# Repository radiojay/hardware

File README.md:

RadioJay Hardware Design
========================

This repo has various hardware designs for RadioJay wildlife tracking tags.
The first few were called "Mostag" for "Motus Open Source TAG" and then later rebranded to RadioJay.
The tags are listed here more or less in reverse chronological order.

For write-ups about these tags see the [RadioJay](https://radiojay.org) web site.

### RadioJay G1 - LoRaWAN+GPS tag

This is a collection of test & dev boards using a bit more space and with connectors to
attach probes and to swap between solar panels and GPS modules.

- [RadioJayG1-ublox](./RadioJayG1-ublox/) has a U-Blox Mia-M10Q GPS and an stm32wle5
  microcontroller with integrated LoRa radio.
- [RadioJayG1-lr1110](./RadioJayG1-lr1110/) has an LR1110 radio with snapshot GPS and with LoRa
  support and uses an stm32u083 microcontroller.
- [RadioJayG1-aem](./RadioJayG1-aem/) is a solar + battery module using an e-Peas AEM10330 energy
  harvesting chip with integrated buck converter; it can be used with a PowerFilm or an IXOLAR
  solar cell and with a LiPO or an LTO battery.
- [RadioJayG1-lr1110](./RadioJayG1-lr1110/) is a solar/battery module using an IXOLAR solar cell
  with an MPP volatge of 4.4V allowing direct charge without boost converter; it has a low Iq
  buck converter to output 1.8V

### RadioJay A2 / MostagV2

First real tag using FlexPCB with a target weight of 1g all-in (incl. loop harness).
Uses uC, Nichicon battery, PowerFilm solar, bq25504, and accelerometer
as well as altimeter (barometer)

#### RadioJay A2a / MostagV2a

Same board with layout changes to satisfy OSH Park's design rules.

### PgmAdapterV2

Adapter board for programming RadioJay A2MostagV2 using a simple USB-serial adapter chip.
Has connectors to attach various types of programming/debug probes.
Most likely not what "normal users" will use, but useful for development.

### RadioJay A1 / MostagV1

Initial proof of concept board, not for strapping to any animal, has uC,
Seiko battery, PowerFilm solar cell, bq25504, and accelerometer, plus linx antenna.

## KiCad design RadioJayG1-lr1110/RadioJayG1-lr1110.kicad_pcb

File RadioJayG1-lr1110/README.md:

RadioJay G1 - LR1110
====================

Test & dev board for a Semtech LR1110, providing GPS snapshot functionality as well as LoRa radio.
A STM32U083 is used as microcontroller for its low power features, familiarity with its peripherals,
and its 256KB flash, which can be used to store GPS data.

The main purpose of the board is to prototype all the pieces and be able to measure power consumption.

Open questions that came up while designing the board:
- Is it possible to get away without 900Mhz RF switch, as one can with the stm32wle?
  The stm32wle datasheet has a footnote in the "sub-Ghz radio characteristics" stating
  "When not in RX operation mode up to 22 dBm is accepted [on RFI_P/RFI_N]". Neither the
  sx1262 nor the lr1110 datasheet have this note so it's not clear whether this is a feature added
  by ST when integrating the sx1262 or whether it's something Semtech doesn't feel the need to specify.
- Can the GPS LNA power be supplied by the LR1110, eliminating one awkward to route signal. The
  datasheet doesn't specify max source current but it does spec minimum V-high voltage @2.5mA,
  which is the typ consumption of the LNA (max is 3.5mA).
- What are the power consumption implications of having only one 32.768kHz xtal and routing the
  clock from the stm32u083 to the LR1110?
- Would rotating the stm32u883 improve the routing?
- What are the minimum RF test points needed in the "final" tag?

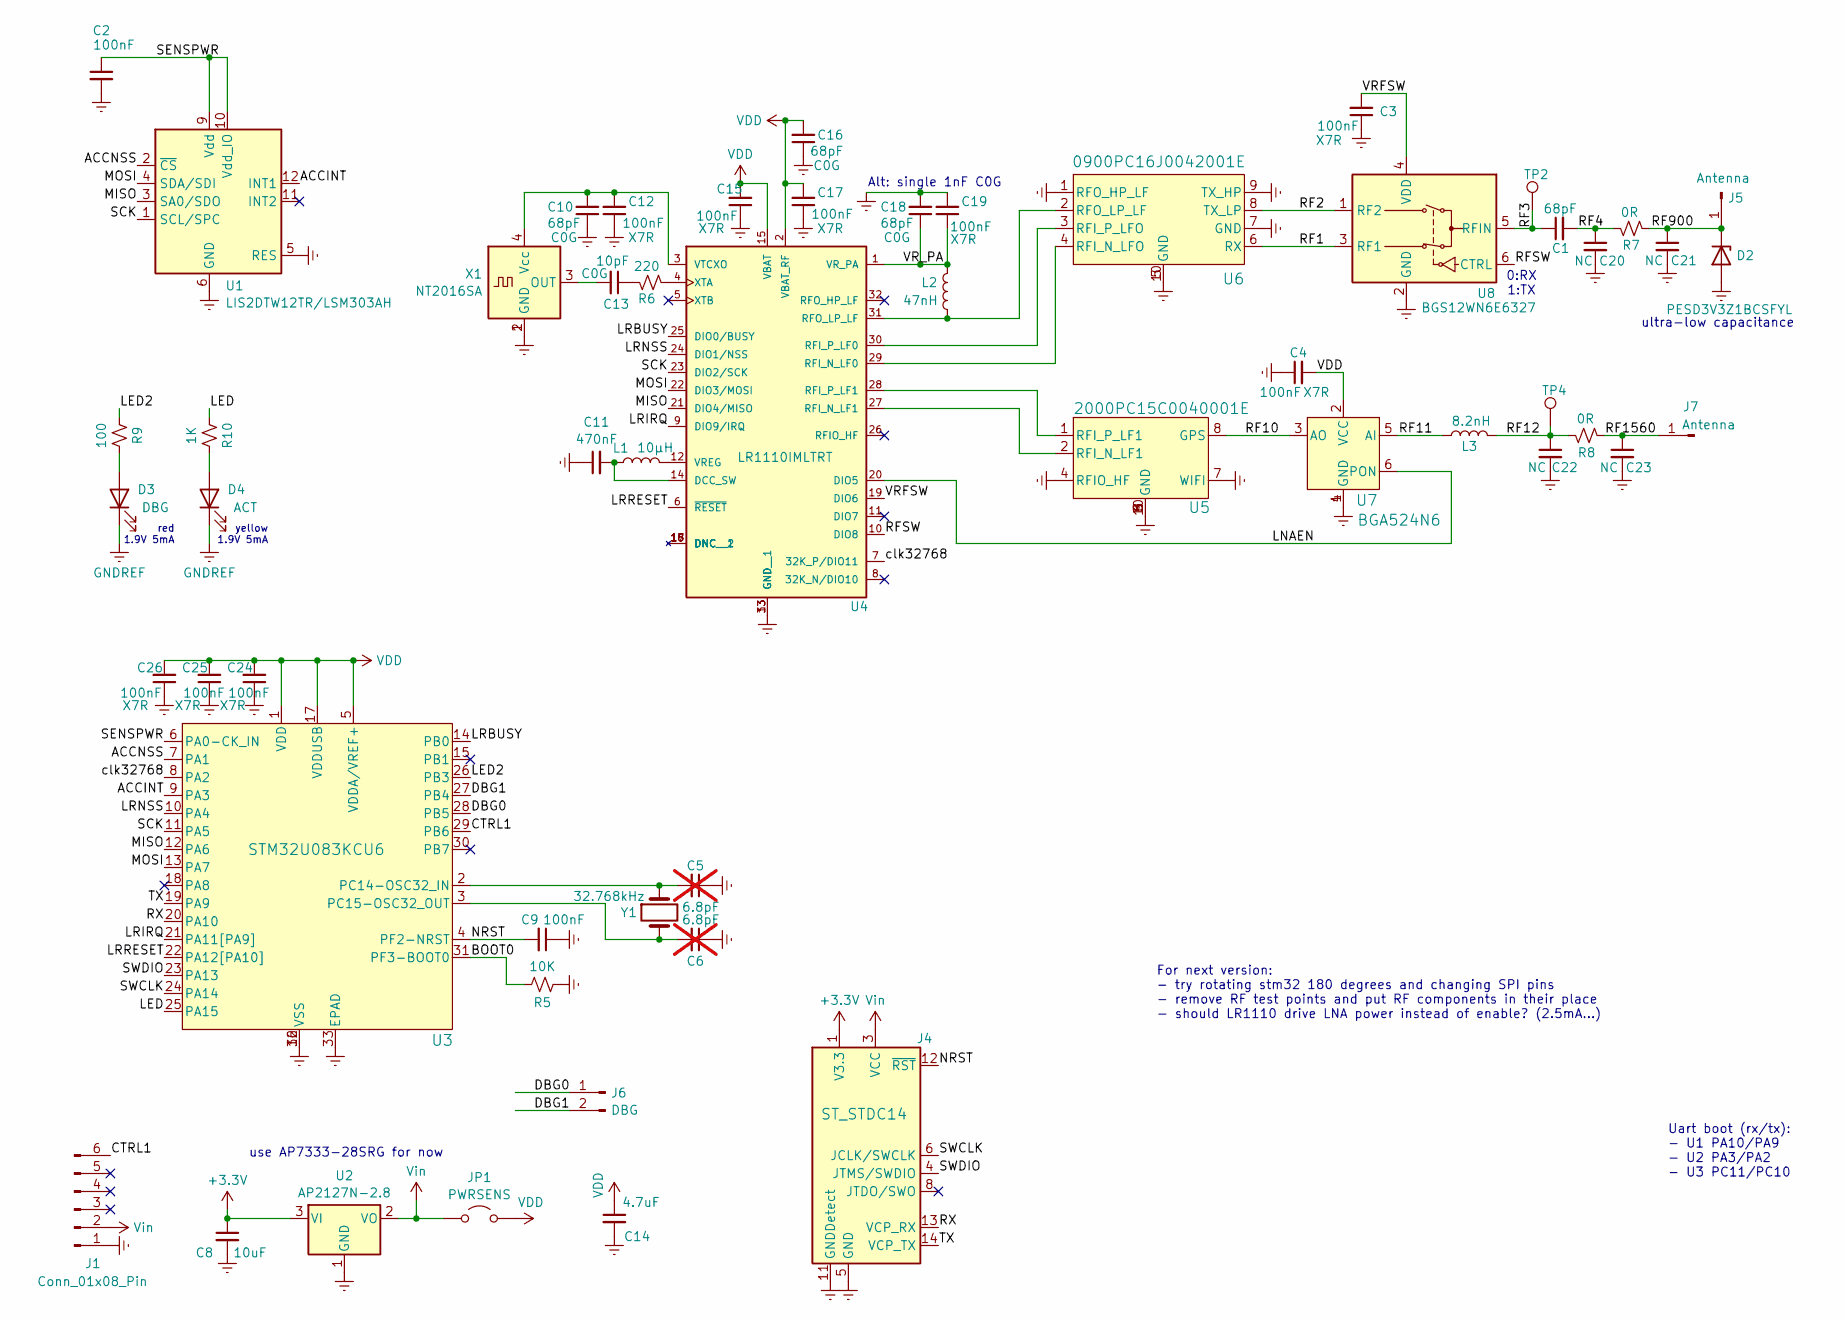
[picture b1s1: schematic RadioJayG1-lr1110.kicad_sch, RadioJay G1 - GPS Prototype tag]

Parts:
C1, C10, C16, C18: 68pF; C_0402_1005Metric
C2, C3, C4, C9, C12, C15, C17, C19, C24, C25, C26: 100nF; C_0402_1005Metric
C5, C6: 6.8pF; C_0402_1005Metric; not fitted
C8: 10uF; C_0603_1608Metric
C11: 470nF; C_0402_1005Metric
C13: 10pF; C_0402_1005Metric
C14: 4.7uF; C_0402_1005Metric
C20, C21, C22, C23: NC; C_0402_1005Metric
D2: PESD3V3Z1BCSFYL; Nexperia_DSN0603-2_0.6x0.3mm_P0.4mm
D3: DBG; LED_0402_1005Metric
D4: ACT; LED_0402_1005Metric
J1: Conn_01x08_Pin; PinHeader_1x06_P2.54mm_Vertical
J4: ST_STDC14; PinHeader_2x07_P1.27mm_Vertical
J5, J7: Antenna; ANT_PAD_2sided_3x2mm
J6: DBG; PinHeader_1x02_P2.54mm_Vertical
JP1: PWRSENS; PinHeader_1x02_P2.54mm_Vertical
L1: 10µH; L_0603_1608Metric; Part MLZ1608N100LT
L2: 47nH; L_0402_1005Metric; Part LQW15AN56NG00
L3: 8.2nH; L_0402_1005Metric; Part LQW
R5: 10K; R_0402_1005Metric
R6: 220; R_0402_1005Metric
R7, R8: 0R; R_0402_1005Metric
R9: 100; R_0402_1005Metric
R10: 1K; R_0402_1005Metric
TP2, TP4: TestPoint; TestPoint_Pad_D1.0mm
U1: LIS2DTW12TR/LSM303AH; LGA-12_2x2mm_P0.5mm
U2: AP2127N-2.8; SOT-23
U3: STM32U083KCU6; UFQFPN-32_STM
U4: LR1110IMLTRT; QFN50P500X500X100-33N; PARTREV 1.3
U5: 2000PC15C0040001E; Johanson-2000PC15
U6: 0900PC16J0042001E; Johanson-0900PC16
U7: BGA524N6; PG-TSNP-6-2_INF
U8: BGS12WN6E6327; Infineon_PG-TSNP-6-10_0.7x1.1mm_0.7x1.1mm_P0.4mm
X1: NT2016SA; Crystal_SMD_2016-4Pin_2.0x1.6mm
Y1: 32.768kHz; Crystal_SMD_2012-2Pin_2.0x1.2mm

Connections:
+3.3V: C8.1, J4.1 (V3.3), U2.3 (VI)
/ACCINT: U1.12 (INT1), U3.9 (PA3)
/ACCNSS: U1.2 (~CS), U3.7 (PA1)
/BOOT0: R5.2, U3.31 (PF3-BOOT0)
/CTRL1: J1.6, U3.29 (PB6)
/DBG0: J6.1, U3.28 (PB5)
/DBG1: J6.2, U3.27 (PB4)
/LED: R10.1, U3.25 (PA15)
/LED2: R9.1, U3.26 (PB3)
/LNAEN: U4.20 (DIO5), U7.6 (PON)
/LRBUSY: U3.14 (PB0), U4.25 (DIO0/BUSY)
/LRIRQ: U3.21 (PA11[PA9]), U4.9 (DIO9/IRQ)
/LRNSS: U3.10 (PA4), U4.24 (DIO1/NSS)
/LRRESET: U3.22 (PA12[PA10]), U4.6 (~RESET)
/MISO: U1.3 (SA0/SDO), U3.12 (PA6), U4.21 (DIO4/MISO)
/MOSI: U1.4 (SDA/SDI), U3.13 (PA7), U4.22 (DIO3/MOSI)
/NRST: C9.2, J4.12 (~RST), U3.4 (PF2-NRST)
/RF1: U6.6 (RX), U8.3 (RF1)
/RF2: U6.8 (TX_LP), U8.1 (RF2)
/RF3: C1.1, TP2.1, U8.5 (RFIN)
/RF4: C1.2, C20.1, R7.2
/RF10: U5.8 (GPS), U7.3 (AO)
/RF11: L3.1, U7.5 (AI)
/RF12: C22.1, L3.2, R8.2, TP4.1
/RF900: C21.1, D2.1 (K), J5.1, R7.1
/RF1560: C23.1, J7.1, R8.1
/RFSW: U4.10 (DIO8), U8.6 (CTRL)
/RX: J4.13 (VCP_RX), U3.20 (PA10)
/SCK: U1.1 (SCL/SPC), U3.11 (PA5), U4.23 (DIO2/SCK)
/SENSPWR: C2.1, U1.9 (Vdd), U1.10 (Vdd_IO), U3.6 (PA0-CK_IN)
/SWCLK: J4.6 (JCLK/SWCLK), U3.24 (PA14)
/SWDIO: J4.4 (JTMS/SWDIO), U3.23 (PA13)
/TX: J4.14 (VCP_TX), U3.19 (PA9)
/VRFSW: C3.2, U4.19 (DIO6), U8.4 (VDD)
/VR_PA: C18.1, C19.1, L2.2, U4.1 (VR_PA)
/clk32768: U3.8 (PA2), U4.7 (32K_P/DIO11)
GNDREF: C2.2, C3.1, C4.1, C5.1, C6.1, C8.2, C9.1, C10.1, C11.1, C12.1, C14.2, C15.1, C16.1, C17.1, C18.2, C19.2, C20.2, C21.2, C22.2, C23.2, C24.1, C25.1, C26.1, D2.2 (A), D3.1 (K), D4.1 (K), J1.1, J4.5 (GND), J4.7 (GND), J4.10 (JTDI/NC), J4.11 (GNDDetect), R5.1, U1.5 (RES), U1.6 (GND), U1.7 (GND), U1.8 (GND), U2.1 (GND), U3.16 (VSS), U3.32 (VSS), U3.33 (EPAD), U4.13 (GND), U4.33 (GND__1), U5.3 (GND), U5.4 (RFIO_HF), U5.5 (GND), U5.6 (GND), U5.7 (WIFI), U5.9 (GND), U5.10 (GND), U6.1 (RFO_HP_LF), U6.5 (GND), U6.7 (GND), U6.9 (TX_HP), U6.10 (GND), U7.1 (GND), U7.4 (GND), U8.2 (GND), X1.1 (GND), X1.2 (GND)
unnamed: C13.1, R6.2
unnamed: D3.2 (A), R9.2
unnamed: D4.2 (A), R10.2
unnamed: C5.2, U3.2 (PC14-OSC32_IN), Y1.1
unnamed: C6.2, U3.3 (PC15-OSC32_OUT), Y1.2
unnamed: C11.2, L1.1, U4.14 (DCC_SW)
unnamed: U4.29 (RFI_N_LF0), U6.4 (RFI_N_LFO)
unnamed: U4.27 (RFI_N_LF1), U5.2 (RFI_N_LF1)
unnamed: U4.30 (RFI_P_LF0), U6.3 (RFI_P_LFO)
unnamed: U4.28 (RFI_P_LF1), U5.1 (RFI_P_LF1)
unnamed: L2.1, U4.31 (RFO_LP_LF), U6.2 (RFO_LP_LF)
unnamed: L1.2, U4.12 (VREG)
unnamed: C10.2, C12.2, U4.3 (VTCXO), X1.4 (Vcc)
unnamed: R6.1, U4.4 (XTA)
unnamed: C13.2, X1.3 (OUT)
VDD: C4.2, C14.1, C15.2, C16.2, C17.2, C24.2, C25.2, C26.2, JP1.2 (B), U3.1 (VDD), U3.5 (VDDA/VREF+), U3.17 (VDDUSB), U4.2 (VBAT_RF), U4.15 (VBAT), U7.2 (VCC)
Vin: J1.2, J4.3 (VCC), JP1.1 (A), U2.2 (VO)

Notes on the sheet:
0:RX 1:TX
use AP7333-28SRG for now
red 1.9V 5mA
yellow 1.9V 5mA
ultra-low capacitance
Uart boot (rx/tx): - U1 PA10/PA9 - U2 PA3/PA2 - U3 PC11/PC10
Alt: single 1nF C0G
For next version: - try rotating stm32 180 degrees and changing SPI pins - remove RF test points and put RF components in their place - should LR1110 drive LNA power instead of enable? (2.5mA...)

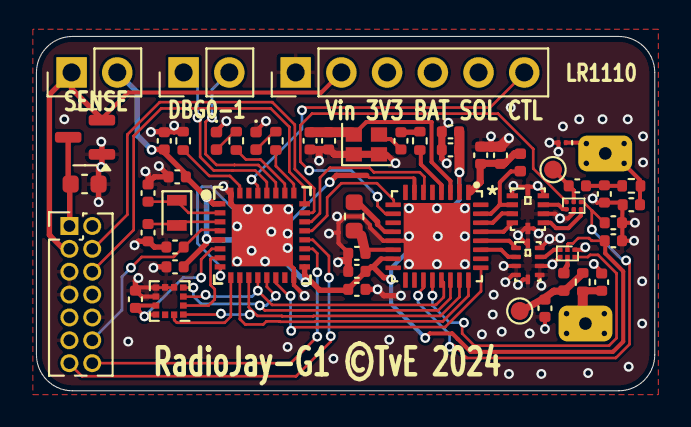
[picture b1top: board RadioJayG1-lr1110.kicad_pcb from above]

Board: 2 copper layers, 34.4 x 19.7 mm, 55 parts (0 on the bottom side), 54 nets.

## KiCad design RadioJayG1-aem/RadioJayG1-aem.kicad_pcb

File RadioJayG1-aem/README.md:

RadioJay G1
===========

Solar / battery module using a low-voltage solar cell (either IXOLAR or PowerFilm) with
E-Peas AEM10330 energy harvesting chip which has a buck converter to output 1.8V.

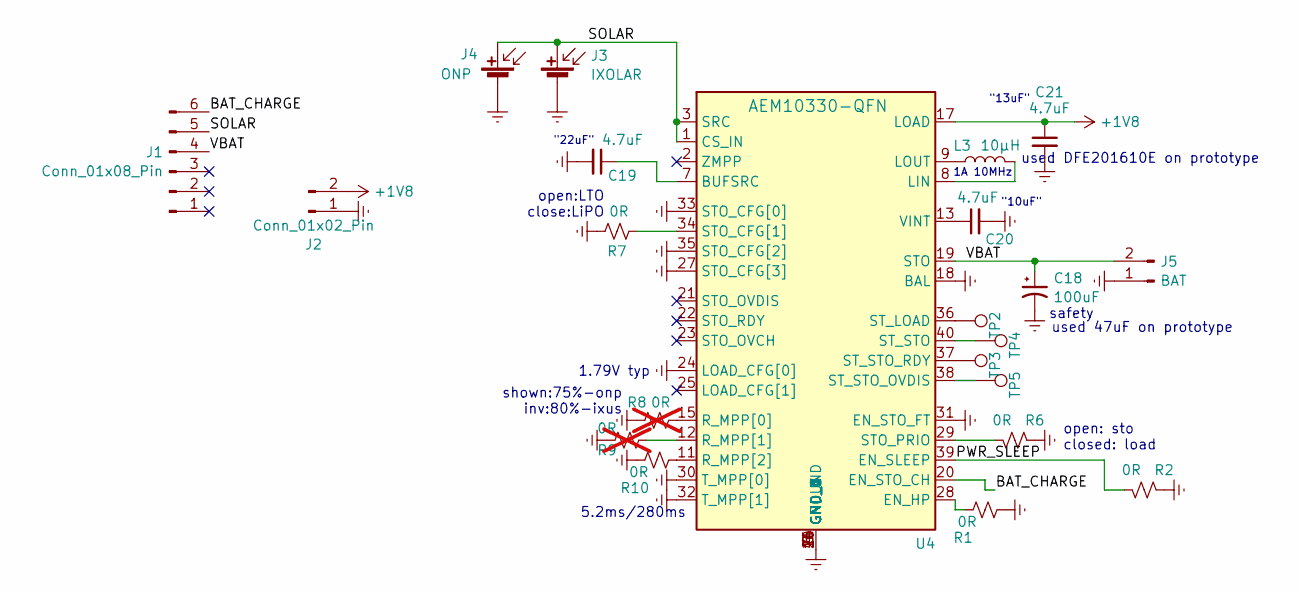
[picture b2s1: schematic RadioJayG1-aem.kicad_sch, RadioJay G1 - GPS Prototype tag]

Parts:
C18: 100uF; C_1206_3216Metric
C19, C20, C21: 4.7uF; C_0603_1608Metric
J1: Conn_01x08_Pin; PinHeader_1x06_P2.54mm_Vertical
J2: Conn_01x02_Pin; PinHeader_1x02_P2.54mm_Vertical
J3: IXOLAR; IXOLAR-23x8
J4: ONP; SOLAR_ONP1.2-cut-12x18
J5: BAT; LiPO-tabs-top-5mm
L3: 10µH; L_0805_2012Metric; Part MLZ2012M150W
R1, R2, R6, R7, R10: 0R; R_0402_1005Metric
R8, R9: 0R; R_0402_1005Metric; not fitted
TP2, TP3, TP4, TP5: TestPoint; TestPoint_Pad_D1.0mm
U4: AEM10330-QFN; QFN40P500X500X85-41N-D; Mouser Part Number 120-AEM10330-QFN

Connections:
+1V8: C21.1, J2.2, U4.17 (LOAD)
/BAT_CHARGE: J1.6, U4.20 (EN_STO_CH)
/PWR_SLEEP: R2.2, U4.39 (EN_SLEEP)
/SOLAR: J1.5, J3.1 (+), J4.1 (+), U4.1 (CS_IN), U4.3 (SRC)
/VBAT: C18.1, J1.4, J5.2, U4.19 (STO)
GNDREF: C18.2, C19.2, C20.2, C21.2, J2.1, J3.2 (-), J4.2 (-), J5.1, R1.2, R2.1, R6.1, R7.1, R8.1, R9.1, R10.1, U4.4 (GND_1), U4.5 (GND_2), U4.6 (GND_3), U4.10 (GND_4), U4.14 (GND_5), U4.16 (GND_6), U4.18 (BAL), U4.24 (LOAD_CFG[0]), U4.26 (GND_7), U4.27 (STO_CFG[3]), U4.30 (T_MPP[0]), U4.31 (EN_STO_FT), U4.32 (T_MPP[1]), U4.33 (STO_CFG[0]), U4.35 (STO_CFG[2]), U4.41 (GROUND)
unnamed: C19.1, U4.7 (BUFSRC)
unnamed: R1.1, U4.28 (EN_HP)
unnamed: L3.2, U4.8 (LIN)
unnamed: L3.1, U4.9 (LOUT)
unnamed: R8.2, U4.15 (R_MPP[0])
unnamed: R9.2, U4.12 (R_MPP[1])
unnamed: R10.2, U4.11 (R_MPP[2])
unnamed: R7.2, U4.34 (STO_CFG[1])
unnamed: R6.2, U4.29 (STO_PRIO)
unnamed: TP2.1, U4.36 (ST_LOAD)
unnamed: TP4.1, U4.40 (ST_STO)
unnamed: TP5.1, U4.38 (ST_STO_OVDIS)
unnamed: TP3.1, U4.37 (ST_STO_RDY)
unnamed: C20.1, U4.13 (VINT)

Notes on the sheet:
"13uF"
5.2ms/280ms
1A 10MHz
shown:75%-onp inv:80%-ixus
safety
used 47uF on prototype
"22uF"
open:LTO close:LiPO
used DFE201610E on prototype
1.79V typ
open: sto closed: load
"10uF"

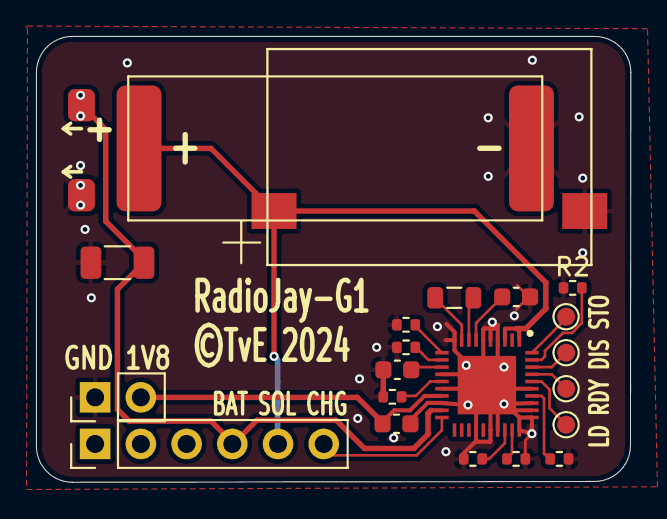
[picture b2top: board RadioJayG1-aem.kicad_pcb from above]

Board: 2 copper layers, 33.0 x 24.8 mm, 22 parts (0 on the bottom side), 20 nets.

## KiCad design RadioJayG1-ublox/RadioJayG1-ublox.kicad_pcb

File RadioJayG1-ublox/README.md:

RadioJay G1
===========

Test & dev board for U-Blox Mia10Q GPS with stm32wle5 microcontroller and integrated LoRa radio.
This board needs to be powered at 1.8V due to the Mia-M10Q
(which could alternatively be powered at 3.3V).

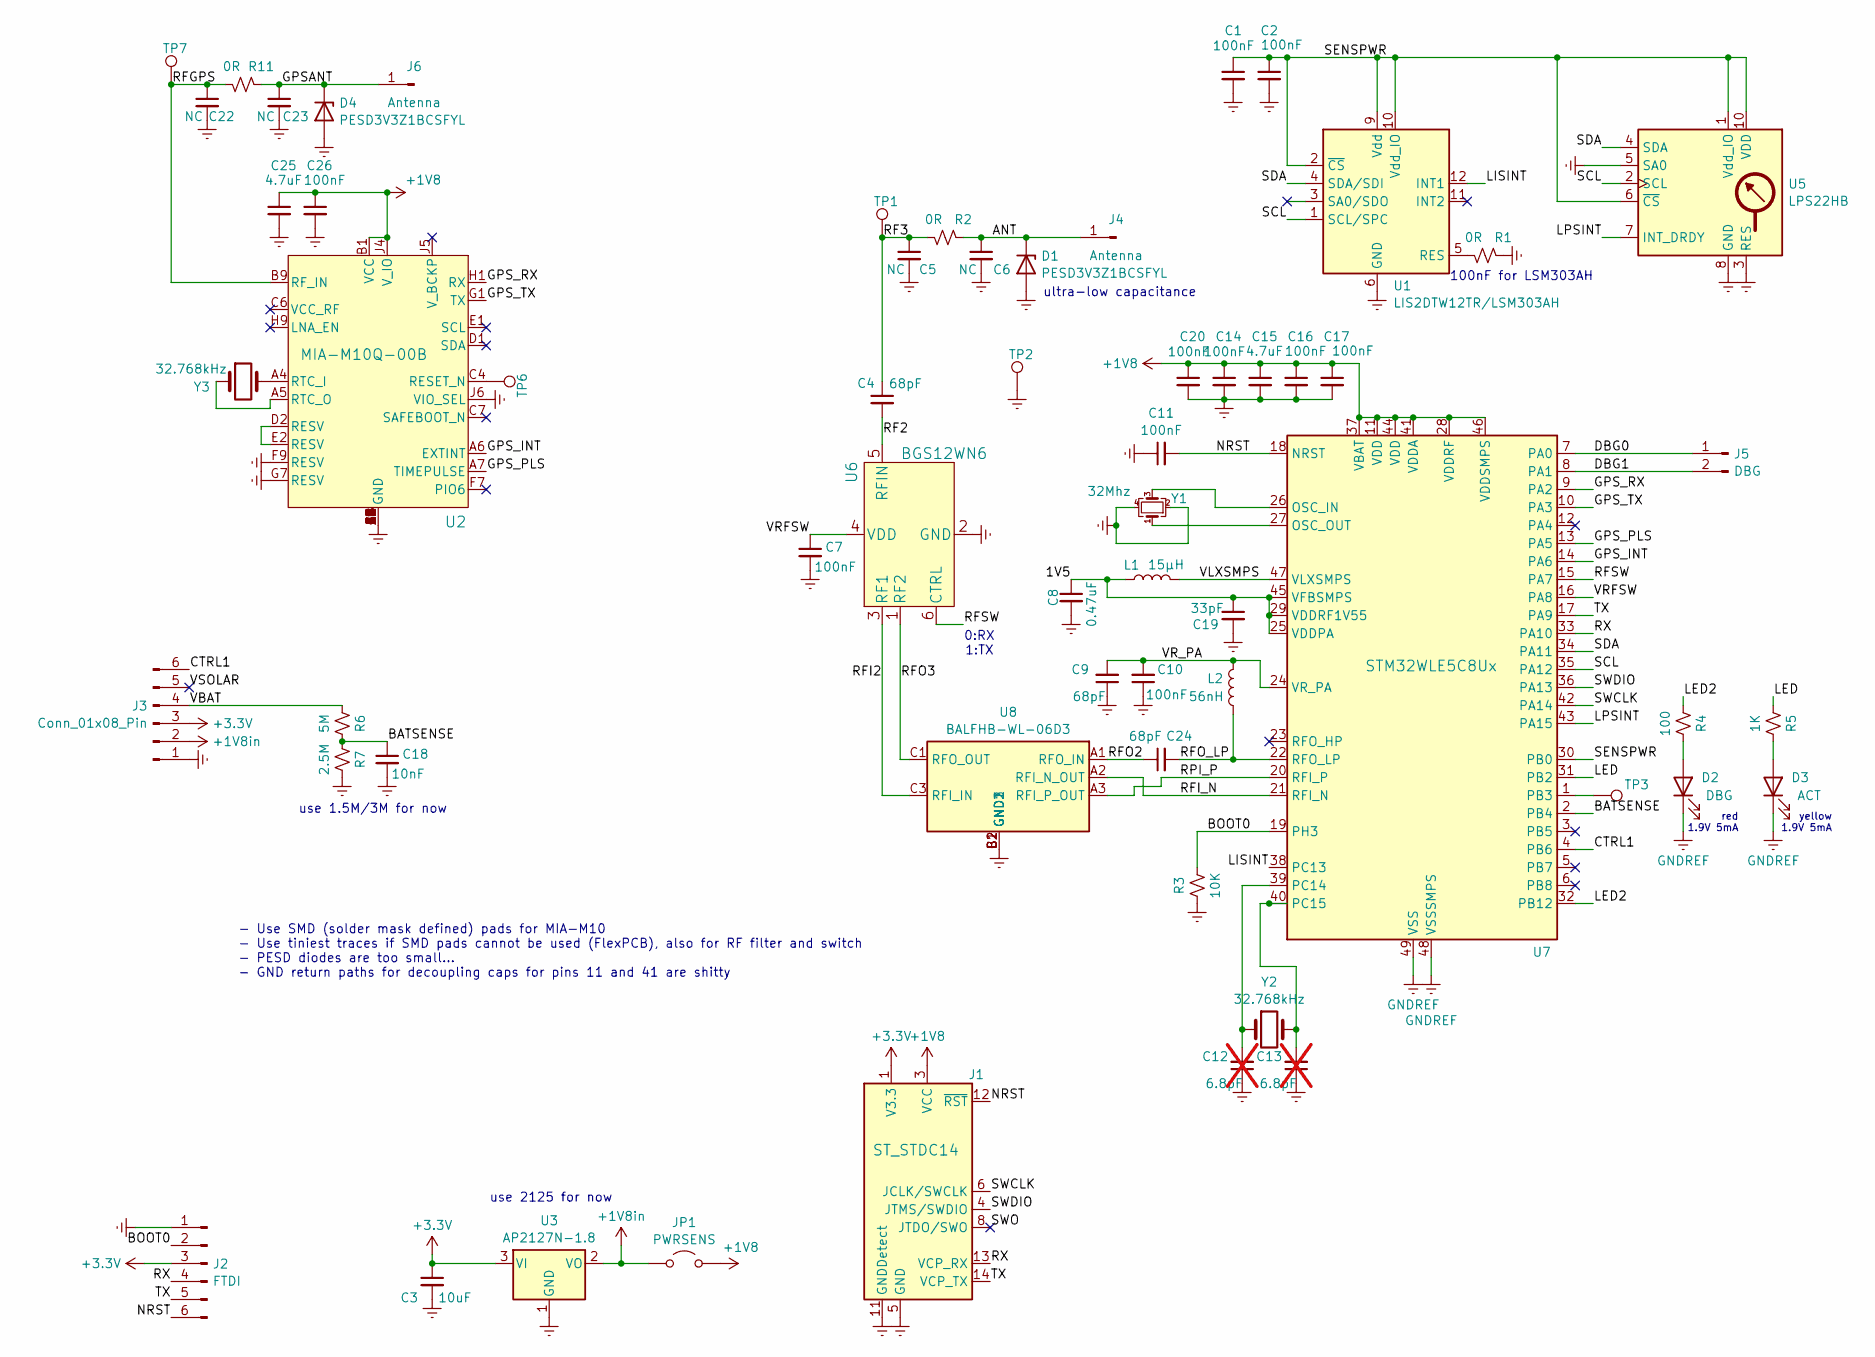
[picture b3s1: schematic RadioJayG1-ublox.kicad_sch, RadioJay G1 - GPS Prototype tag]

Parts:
C1, C2, C7, C10, C11, C14, C16, C17, C20, C26: 100nF; C_0402_1005Metric
C3: 10uF; C_0603_1608Metric
C4, C9, C24: 68pF; C_0402_1005Metric
C5, C6, C22, C23: NC; C_0402_1005Metric
C8: 0.47uF; C_0402_1005Metric
C12, C13: 6.8pF; C_0402_1005Metric; not fitted
C15, C25: 4.7uF; C_0402_1005Metric
C18: 10nF; C_0402_1005Metric
C19: 33pF; C_0402_1005Metric
D1, D4: PESD3V3Z1BCSFYL; Nexperia_DSN0603-2_0.6x0.3mm_P0.4mm
D2: DBG; LED_0402_1005Metric
D3: ACT; LED_0402_1005Metric
J1: ST_STDC14; PinHeader_2x07_P1.27mm_Vertical
J2: FTDI; PinHeader_1x06_P2.54mm_Vertical
J3: Conn_01x08_Pin; PinHeader_1x06_P2.54mm_Vertical
J4, J6: Antenna; ANT_PAD_2sided_3x2mm
J5: DBG; PinHeader_1x02_P2.54mm_Vertical
JP1: PWRSENS; PinHeader_1x02_P2.54mm_Vertical
L1: 15µH; L_0805_2012Metric; Part MLZ2012M150W
L2: 56nH; L_0402_1005Metric; Part LQW15AN56NG00
R1, R2, R11: 0R; R_0402_1005Metric
R3: 10K; R_0402_1005Metric
R4: 100; R_0402_1005Metric
R5: 1K; R_0402_1005Metric
R6: 5M; R_0402_1005Metric
R7: 2.5M; R_0402_1005Metric
TP1, TP2, TP6, TP7: TestPoint; TestPoint_Pad_D1.0mm
TP3: TestPoint; TestPoint_Pad_1.0x0.5mm
U1: LIS2DTW12TR/LSM303AH; LGA-12_2x2mm_P0.5mm
U2: MIA-M10Q-00B; LGA_M10Q-00B_UBL
U3: AP2127N-1.8; SOT-23
U5: LPS22HB; HLGA-10L_2X2X0P73_STM
U6: BGS12WN6; PG-TSNP-6-10_INF
U7: STM32WLE5C8Ux; QFN-48-1EP_7x7mm_P0.5mm_EP5.6x5.6mm
U8: BALFHB-WL-06D3; BALFHBWL06D3; Mouser Part Number 511-BALFHB-WL-06D3
Y1: 32Mhz; Crystal_SMD_2016-4Pin_2.0x1.6mm; Part NX2016SA-32Mhz (CS06465-32M)
Y2, Y3: 32.768kHz; Crystal_SMD_2012-2Pin_2.0x1.2mm

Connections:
+1V8: C14.1, C15.1, C16.1, C17.1, C20.1, C25.1, C26.1, J1.3 (VCC), JP1.2 (B), U2.B1 (VCC), U2.J4 (V_IO), U7.11 (VDD), U7.28 (VDDRF), U7.37 (VBAT), U7.41 (VDDA), U7.44 (VDD), U7.46 (VDDSMPS)
+1V8in: J3.2, JP1.1 (A), U3.2 (VO)
+3.3V: C3.1, J1.1 (V3.3), J2.3, J3.3, U3.3 (VI)
/1V5: C8.1, C19.1, L1.1, U7.25 (VDDPA), U7.29 (VDDRF1V55), U7.45 (VFBSMPS)
/ANT: C6.1, D1.1 (K), J4.1, R2.1
/BATSENSE: C18.1, R6.2, R7.1, U7.2 (PB4)
/BOOT0: J2.2, R3.2, U7.19 (PH3)
/CTRL1: J3.6, U7.4 (PB6)
/DBG0: J5.1, U7.7 (PA0)
/DBG1: J5.2, U7.8 (PA1)
/GPSANT: C23.1, D4.1 (K), J6.1, R11.1
/GPS_INT: U2.A6 (EXTINT), U7.14 (PA6)
/GPS_PLS: U2.A7 (TIMEPULSE), U7.13 (PA5)
/GPS_RX: U2.H1 (RX), U7.9 (PA2)
/GPS_TX: U2.G1 (TX), U7.10 (PA3)
/LED: R5.1, U7.31 (PB2)
/LED2: R4.1, U7.32 (PB12)
/LISINT: U1.12 (INT1), U7.38 (PC13)
/LPSINT: U5.7 (INT_DRDY), U7.43 (PA15)
/NRST: C11.2, J1.12 (~RST), J2.6, U7.18 (NRST)
/RF2: C4.2, U6.5 (RFIN)
/RF3: C4.1, C5.1, R2.2, TP1.1
/RFGPS: C22.1, R11.2, TP7.1, U2.B9 (RF_IN)
/RFI2: U6.3 (RF1), U8.C3 (RFI_IN)
/RFI_N: U7.21 (RFI_N), U8.A2 (RFI_N_OUT)
/RFO2: C24.1, U8.A1 (RFO_IN)
/RFO3: U6.1 (RF2), U8.C1 (RFO_OUT)
/RFO_LP: C24.2, L2.1, U7.22 (RFO_LP)
/RFSW: U6.6 (CTRL), U7.15 (PA7)
/RPI_P: U7.20 (RFI_P), U8.A3 (RFI_P_OUT)
/RX: J1.13 (VCP_RX), J2.4, U7.33 (PA10)
/SCL: U1.1 (SCL/SPC), U5.2 (SCL), U7.35 (PA12)
/SDA: U1.4 (SDA/SDI), U5.4 (SDA), U7.34 (PA11)
/SENSPWR: C1.1, C2.1, U1.2 (~CS), U1.9 (Vdd), U1.10 (Vdd_IO), U5.1 (Vdd_IO), U5.6 (~CS), U5.10 (VDD), U7.30 (PB0)
/SWCLK: J1.6 (JCLK/SWCLK), U7.42 (PA14)
/SWDIO: J1.4 (JTMS/SWDIO), U7.36 (PA13)
/SWO: J1.8 (JTDO/SWO)
/TX: J1.14 (VCP_TX), J2.5, U7.17 (PA9)
/VBAT: J3.4, R6.1
/VLXSMPS: L1.2, U7.47 (VLXSMPS)
/VRFSW: C7.1, U6.4 (VDD), U7.16 (PA8)
/VR_PA: C9.2, C10.2, L2.2, U7.24 (VR_PA)
/VSOLAR: J3.5
GNDREF: C1.2, C2.2, C3.2, C5.2, C6.2, C7.2, C8.2, C9.1, C10.1, C11.1, C12.1, C13.1, C14.2, C15.2, C16.2, C17.2, C18.2, C19.2, C20.2, C22.2, C23.2, C25.2, C26.2, D1.2 (A), D2.1 (K), D3.1 (K), D4.2 (A), J1.5 (GND), J1.7 (GND), J1.10 (JTDI/NC), J1.11 (GNDDetect), J2.1, J3.1, R1.1, R3.1, R7.2, TP2.1, U1.6 (GND), U1.7 (GND), U1.8 (GND), U2.A1 (GND), U2.A2 (GND), U2.A3 (GND), U2.A8 (GND), U2.A9 (GND), U2.B2 (GND), U2.B8 (GND), U2.C3 (GND), U2.C9 (GND), U2.E3 (GND), U2.E4 (GND), U2.E9 (GND), U2.F1 (GND), U2.F3 (GND), U2.F4 (GND), U2.F9 (RESV), U2.G3 (GND), U2.G4 (GND), U2.G5 (GND), U2.G6 (GND), U2.G7 (RESV), U2.H8 (GND), U2.J6 (VIO_SEL), U2.J8 (GND), U2.J9 (GND), U3.1 (GND), U5.3 (RES), U5.5 (SA0), U5.8 (GND), U5.9 (GND), U6.2 (GND), U7.48 (VSSSMPS), U7.49 (VSS), U8.B1 (GND2), U8.B2 (GND3), U8.C2 (GND1), Y1.2, Y1.4
unnamed: D2.2 (A), R4.2
unnamed: D3.2 (A), R5.2
unnamed: R1.2, U1.5 (RES)
unnamed: TP6.1, U2.C4 (RESET_N)
unnamed: U2.D2 (RESV), U2.E2 (RESV)
unnamed: U2.A4 (RTC_I), Y3.2
unnamed: U2.A5 (RTC_O), Y3.1
unnamed: U7.26 (OSC_IN), Y1.3
unnamed: U7.27 (OSC_OUT), Y1.1
unnamed: TP3.1, U7.1 (PB3)
unnamed: C12.2, U7.39 (PC14), Y2.1
unnamed: C13.2, U7.40 (PC15), Y2.2

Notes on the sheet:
- Use SMD (solder mask defined) pads for MIA-M10 - Use tiniest traces if SMD pads cannot be used (FlexPCB), also for RF filter and switch - PESD diodes are too small... - GND return paths for decoupling caps for pins 11 and 41 are shitty
use 2125 for now
use 1.5M/3M for now
red 1.9V 5mA
yellow 1.9V 5mA
ultra-low capacitance
0:RX 1:TX
100nF for LSM303AH

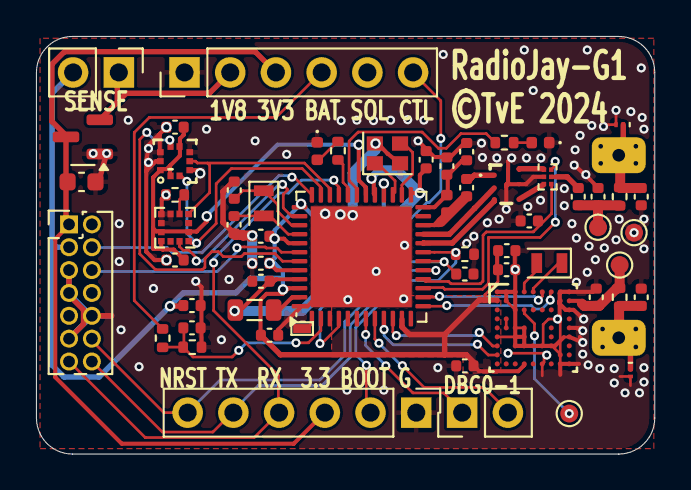
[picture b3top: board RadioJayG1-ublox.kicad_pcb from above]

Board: 2 copper layers, 34.4 x 23.2 mm, 61 parts (0 on the bottom side), 54 nets.

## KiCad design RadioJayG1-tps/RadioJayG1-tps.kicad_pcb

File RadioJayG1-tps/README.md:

RadioJay G1
===========

Solar power test board using a solar panel with a MPP voltage around 4.4V allowing direct
charge of a LiPO battery without boost charger.
A high side power switch is used to end the charge and a switching power supply with extremely 
low Iq is used to output 1.8V.

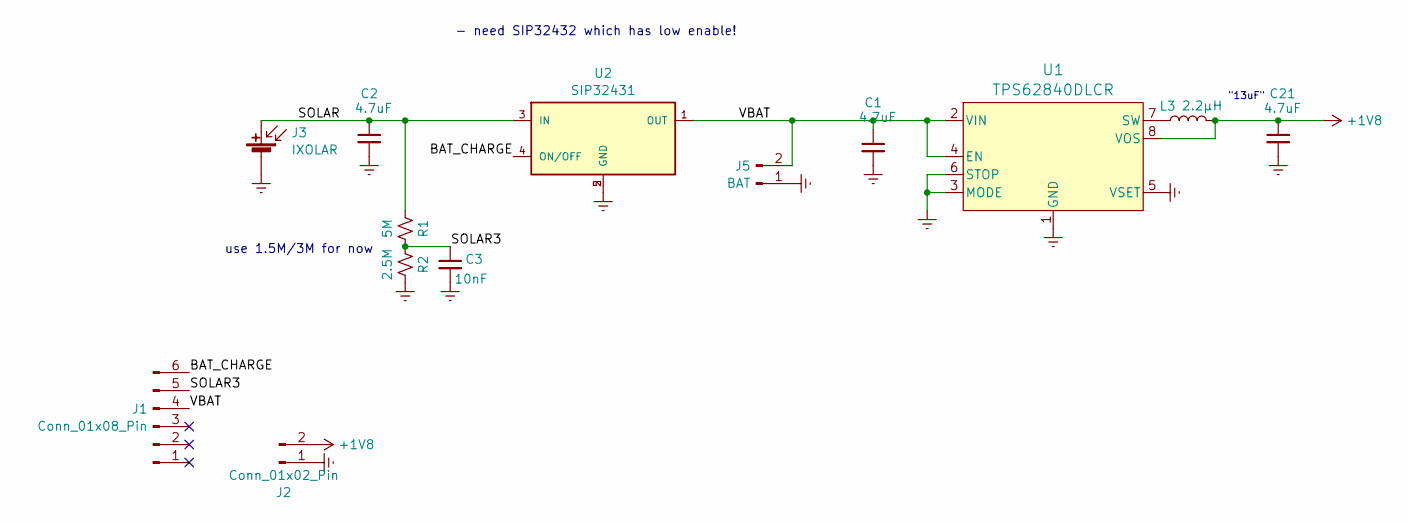
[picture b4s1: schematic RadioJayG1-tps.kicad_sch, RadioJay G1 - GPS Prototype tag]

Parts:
C1, C2, C21: 4.7uF; C_0603_1608Metric
C3: 10nF; C_0402_1005Metric
J1: Conn_01x08_Pin; PinHeader_1x06_P2.54mm_Vertical
J2: Conn_01x02_Pin; PinHeader_1x02_P2.54mm_Vertical
J3: IXOLAR; IXOLAR-23x8
J5: BAT; LiPO-tabs-top-5mm
L3: 2.2µH; L_0805_2012Metric; Part MLZ2012M150W
R1: 5M; R_0402_1005Metric
R2: 2.5M; R_0402_1005Metric
U1: TPS62840DLCR; VSON8_2P1X1P6_TEX
U2: SIP32431; DFN_NP3-T1GE4_VIS

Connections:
+1V8: C21.1, J2.2, L3.2, U1.8 (VOS)
/BAT_CHARGE: J1.6, U2.4 (ON/OFF)
/SOLAR: C2.1, J3.1 (+), R1.1, U2.3 (IN)
/SOLAR3: C3.1, J1.5, R1.2, R2.1
/VBAT: C1.1, J1.4, J5.2, U1.2 (VIN), U1.4 (EN), U2.1 (OUT)
GNDREF: C1.2, C2.2, C3.2, C21.2, J2.1, J3.2 (-), J5.1, R2.2, U1.1 (GND), U1.3 (MODE), U1.5 (VSET), U1.6 (STOP), U2.2 (GND), U2.5 (GND)
unnamed: L3.1, U1.7 (SW)

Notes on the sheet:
"13uF"
- need SIP32432 which has low enable!
use 1.5M/3M for now

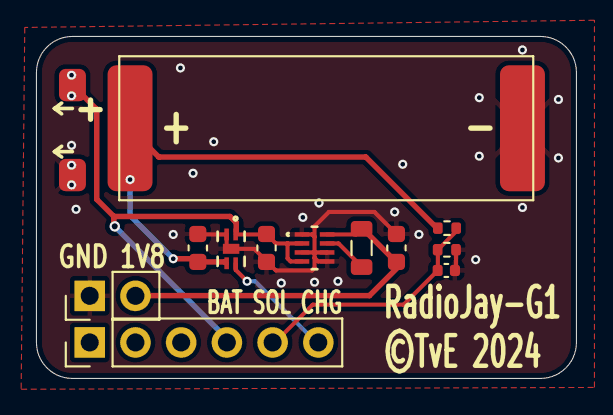
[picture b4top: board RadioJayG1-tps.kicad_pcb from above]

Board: 2 copper layers, 30.0 x 19.0 mm, 13 parts (0 on the bottom side), 7 nets.

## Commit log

2024-10-12 add RagioJayG1 versions
2024-10-13 fixes
2024-10-13 Create LICENSE

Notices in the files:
RadioJayG1-aem/RadioJayG1-aem.kicad_pcb:
©TvE 2024
RadioJayG1-lr1110/RadioJayG1-lr1110.kicad_pcb:
RadioJay-G1 ©TvE 2024
